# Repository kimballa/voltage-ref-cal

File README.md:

Voltage reference calibration tool
==================================

Precision referenced voltages in 1.000V increments for calibration
of exponential converters in VCOs, VCFs, etc. 

Also usable as a manual GATE/TRIGGER signal generator.

View drawings online:
* [Schematic](https://github.com/kimballa/voltage-ref-cal/blob/main/schematic-rev1.pdf)
* [PCB](https://kicanvas.org/?github=https%3A%2F%2Fgithub.com%2Fkimballa%2Fvoltage-ref-cal%2Fblob%2Fmain%2Fvoltage%2520ref%2520calibration%2520tool.kicad_pcb)

Operation
---------

The rotary switch selects the "baseline voltage" for the output (mono jack J3 and dupont
pins J4), and can set the baseline to between 0 and 5V in 1V increments. 

When pressed, the buttons add further voltages to this; setting the baseline to 4V and
pressing the 2V button will cause the output to jump to 6V. Pressing multiple buttons
at once will sum them up; pressing the 2V and 1V buttons will add 3V to the baseline
as sent to the output, etc. 

The **REF IN** input (J1) takes a voltage input and buffers it; this voltage will be
added to the output when the +IN button is pressed. This reference input voltage can be
any voltage between the power rails, including negative voltages down to -12V.

This device is powered by +/-12VDC input via the Molex MicroFit 3.0 connector J2.  Setting
the power rails at up to +/-18V is acceptable; above this voltage level, the Zener diodes
will exceed power dissipation ratings.  The opamp will also tolerate this level just fine.

Calibration
-----------

Before use, adjust trimpots RV1 and RV2 as follows:

* Set baseline to 5V.
* Give circuit ~60 seconds to warm up.
* Measure output voltage with a DMM.
* Adjust RV1 until output (or test point TP4) reads 5.000V.
* Set baseline to 0V.
* While holding down the +5V button, adjust RV2 until output voltage reads 5.000V.
  (Or measure with DMM at test point TP5 without needing to press the +5V button.) 

Usage tips
----------

### VCO calibration

The primary purpose of the device is to assist in calibration of exponential converters
for VCOs, VCFs, or similar audio equipment. Calibration of this equipment is typically to
establish a 1V / Octave frequency response. Use the knob to set the baseline voltage
at the root of a given octave, and press the +1V button to change the output to the next
octave up in a step-function fashion. This output voltage should be fed as the CV to
the VCO.

An oscilloscope connected to the output of the VCO will show the output waveform. If the
1V/Oct response is maintained, pressing the +1V button will double the frequency and (half
of) the zeroes of the double-frequency waveform will be in the exact same position as the
zeroes of the root-frequency waveform.

Increasing the baseline voltage with the knob allows you to test this 1V / 1 octave step
response throughout the range of the DUT. To test beyond the 6th octave, set the baseline
voltage to 4V and hold down the +2V button to set the baseline at 6V, then press the +1V
button to test the 7V response, etc.

### As standalone GATE / Trigger

To test other functionality of a device that requires a GATE or trigger input, set
the baseline to 0V and press the +5V button to send a GATE signal to the DUT. The +3V
button can be used to trigger devices with a 3.3V logic input. 

Misc
----

Output can be taken from the mono jack or from the pins on connector J4. Both pins of
J4 are the same, and allow easy connection via jumper to breadboard, etc., or connection
of hook-style oscilloscope or DMM probes directly to this board. Matching ground
connection pins are available on J5. 

The output sum will top out at approximately +11.75V (possibly as low as +11V if the
output is used to drive a 2kΩ load). 

If no input is provided to the REF IN jack, it is normaled to ground (+IN button will add
0V to the output).

The rotary switch is a 1-pole, 6-position switch, Alpha MPN `SR1712F-0106-20F0A-N9-N-027`.
This device is now marked obsolete by its mfr; I built with this device because I have
several still on hand. Any 1-deck, 1-pole, 6-position BBM switch with 30 degree position
intervals will do, and there is ample space on the board to fit a different switch
footprint with minimal rerouting of traces. Alpha produces other SR1712F rotary switches
like the 8-position `SR1712F-0108` which can also be dropped in directly. (As-is, the 7th
& 8th positions will cause the baseline voltage to float and the output will be undefined
when the switch is in either of these positions; you could cause the output to be defined
by simply connecting those two pins of the switch to ground.)

License
-------
The voltage reference calibration tool © 2024 by Aaron Kimball is licensed under CC BY-SA
4.0. To view a copy of this license, visit https://creativecommons.org/licenses/by-sa/4.0/

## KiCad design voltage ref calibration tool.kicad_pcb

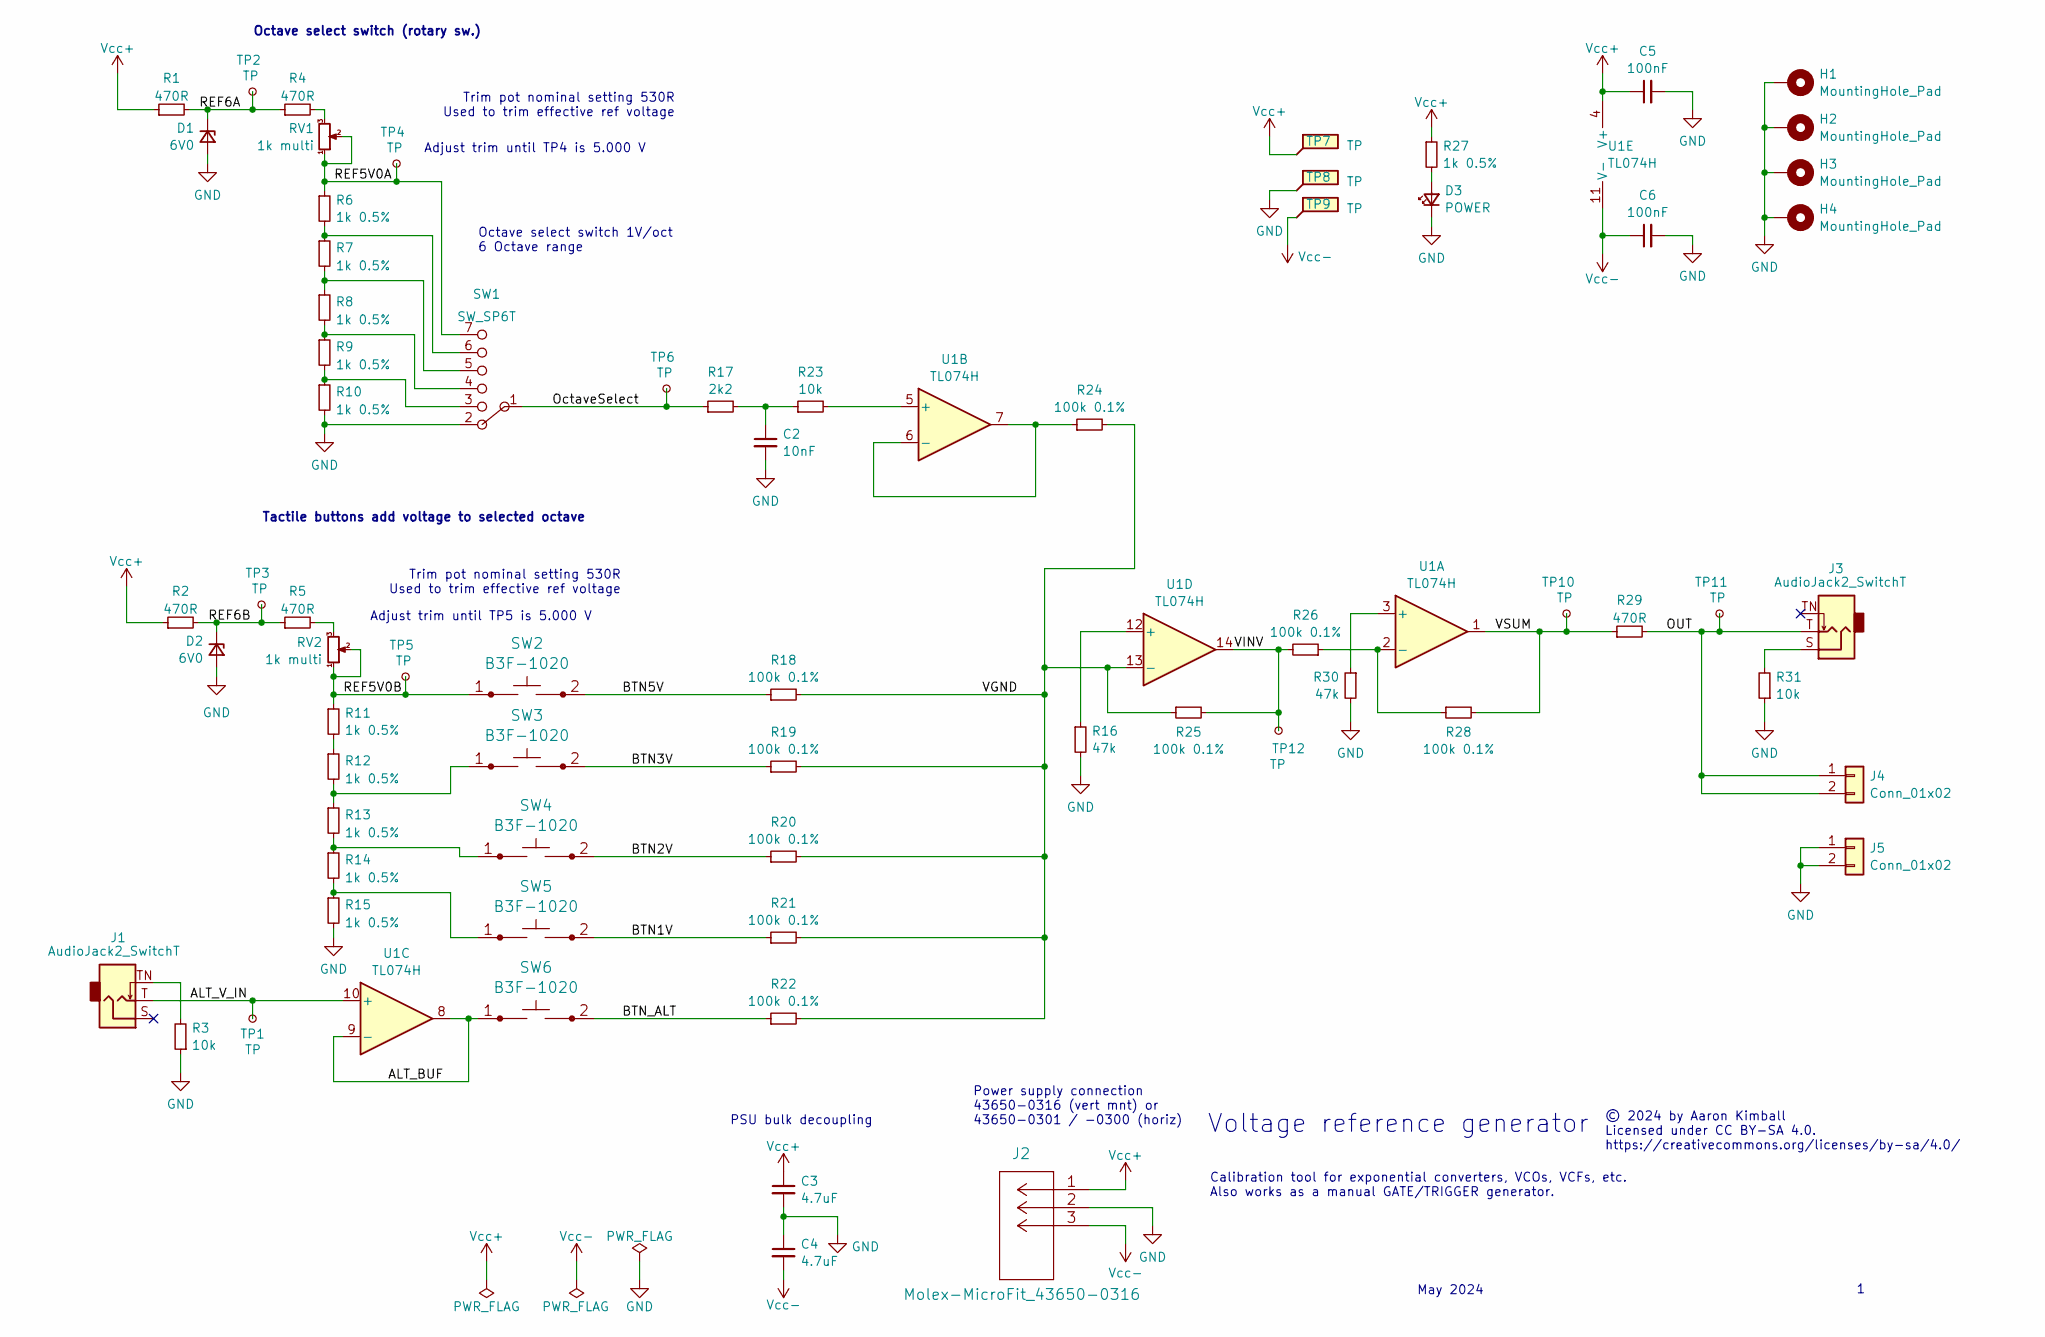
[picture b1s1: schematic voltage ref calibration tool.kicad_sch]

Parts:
C2: 10nF; C_0805_2012Metric_Pad1.18x1.45mm_HandSolder; MPN GRM2165C2A103JA01D
C3, C4: 4.7uF; C_1206_3216Metric_Pad1.33x1.80mm_HandSolder; MPN CL31B475KBHNFNE
C5, C6: 100nF; C_0805_2012Metric_Pad1.18x1.45mm_HandSolder; MPN CL21B104KBFNNNE
D1, D2: 6V0; D_SOD-123_SilkFix; MPN MMSZ5233C-E3-18
D3: POWER; LED_D3.0mm; MPN WP3A8ID
H1, H2, H3, H4: MountingHole_Pad; MountingHole_3.3mm_M3_Full_Standoff_Size
J1, J3: AudioJack2_SwitchT; Schurter-4832.2211; MPN 4832.2211
J2: Molex-MicroFit_43650-0316; Molex-Microfit-43650-0316; MPN 436500316
J4, J5: Conn_01x02; PinHeader_1x02_P2.54mm_Vertical; MPN 5-146850-1
R1, R2, R4, R5, R29: 470R; R_1206_3216Metric_Pad1.30x1.75mm_HandSolder; MPN RC1206FR-7W470RL
R3, R23, R31: 10k; R_0805_2012Metric_Pad1.20x1.40mm_HandSolder; MPN RMCF0805FT10K0
R6, R7, R8, R9, R10, R11, R12, R13, R14, R15, R27: 1k 0.5%; R_1206_3216Metric_Pad1.30x1.75mm_HandSolder; MPN RT1206DRE071KL
R16, R30: 47k; R_0805_2012Metric_Pad1.20x1.40mm_HandSolder; MPN RC0805FR-0747KL
R17: 2k2; R_0805_2012Metric_Pad1.20x1.40mm_HandSolder; MPN CRG0805F2K2
R18, R19, R20, R21, R22, R24, R25, R26, R28: 100k 0.1%; R_0805_2012Metric_Pad1.20x1.40mm_HandSolder; MPN ERA-6AEB104V
RV1, RV2: 1k multi; Pot_Bourns_3214W_SMD_Vert; MPN 3214W-1-102E
SW1: SW_SP6T; Alpha_SR1712F; MPN SR1712F-0106-20F0A-N9-N-027
SW2, SW3, SW4, SW5, SW6: B3F-1020; MPN B3F-1020
TP1, TP2, TP3, TP4, TP5, TP6, TP7, TP8, TP9, TP10, TP11, TP12: TP; TP_HeaderPin_P2.54mm_round
U1: TL074H; TI_SOIC_D_R-PDSO-G14_Wider_Silk; MPN TL074HIDR

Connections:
/ALT_BUF: SW6.1, U1.8, U1.9 (-)
/ALT_V_IN: J1.T, TP1.1, U1.10 (+)
/BTN1V: R21.1, SW5.2
/BTN2V: R20.1, SW4.2
/BTN3V: R19.1, SW3.2
/BTN5V: R18.1, SW2.2
/BTN_ALT: R22.1, SW6.2
/OUT: J3.T, J4.1, J4.2, R29.2, TP11.1
/OctaveSelect: R17.1, SW1.1, TP6.1
/REF5V0A: R6.1, RV1.1, RV1.2, SW1.7, TP4.1
/REF5V0B: R11.1, RV2.1, RV2.2, SW2.1, TP5.1
/REF6A: D1.1 (K), R1.2, R4.1, TP2.1
/REF6B: D2.1 (K), R2.2, R5.1, TP3.1
/VGND: R18.2, R19.2, R20.2, R21.2, R22.2, R24.2, R25.1, U1.13 (-)
/VINV: R25.2, R26.2, TP12.1, U1.14
/VSUM: R28.2, R29.1, TP10.1, U1.1
GND: C2.2, C3.2, C4.1, C5.2, C6.2, D1.2 (A), D2.2 (A), D3.1 (K), H1.1, H2.1, H3.1, H4.1, J2.2, J5.1, J5.2, R3.1, R10.2, R15.2, R16.2, R30.2, R31.1, SW1.2, TP8.1
unnamed: C2.1, R17.2, R23.1
unnamed: D3.2 (A), R27.2
unnamed: J1.TN, R3.2
unnamed: J3.S, R31.2
unnamed: R4.2, RV1.3
unnamed: R5.2, RV2.3
unnamed: R6.2, R7.1, SW1.6
unnamed: R7.2, R8.1, SW1.5
unnamed: R8.2, R9.1, SW1.4
unnamed: R9.2, R10.1, SW1.3
unnamed: R11.2, R12.1
unnamed: R12.2, R13.1, SW3.1
unnamed: R13.2, R14.1, SW4.1
unnamed: R14.2, R15.1, SW5.1
unnamed: R30.1, U1.3 (+)
unnamed: R26.1, R28.1, U1.2 (-)
unnamed: R23.2, U1.5 (+)
unnamed: R24.1, U1.6 (-), U1.7
unnamed: R16.1, U1.12 (+)
Vcc+: C3.1, C5.1, J2.1, R1.1, R2.1, R27.1, TP7.1, U1.4 (V+)
Vcc-: C4.2, C6.1, J2.3, TP9.1, U1.11 (V-)

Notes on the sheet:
May 2024
Trim pot nominal setting 530R Used to trim effective ref voltage
Adjust trim until TP4 is 5.000 V
Octave select switch (rotary sw.)
Power supply connection 43650-0316 (vert mnt) or 43650-0301 / -0300 (horiz)
PSU bulk decoupling
Octave select switch 1V/oct 6 Octave range
© 2024 by Aaron Kimball Licensed under CC BY-SA 4.0. https://creativecommons.org/licenses/by-sa/4.0/
Adjust trim until TP5 is 5.000 V
Calibration tool for exponential converters, VCOs, VCFs, etc. Also works as a manual GATE/TRIGGER generator.
Voltage reference generator
Tactile buttons add voltage to selected octave

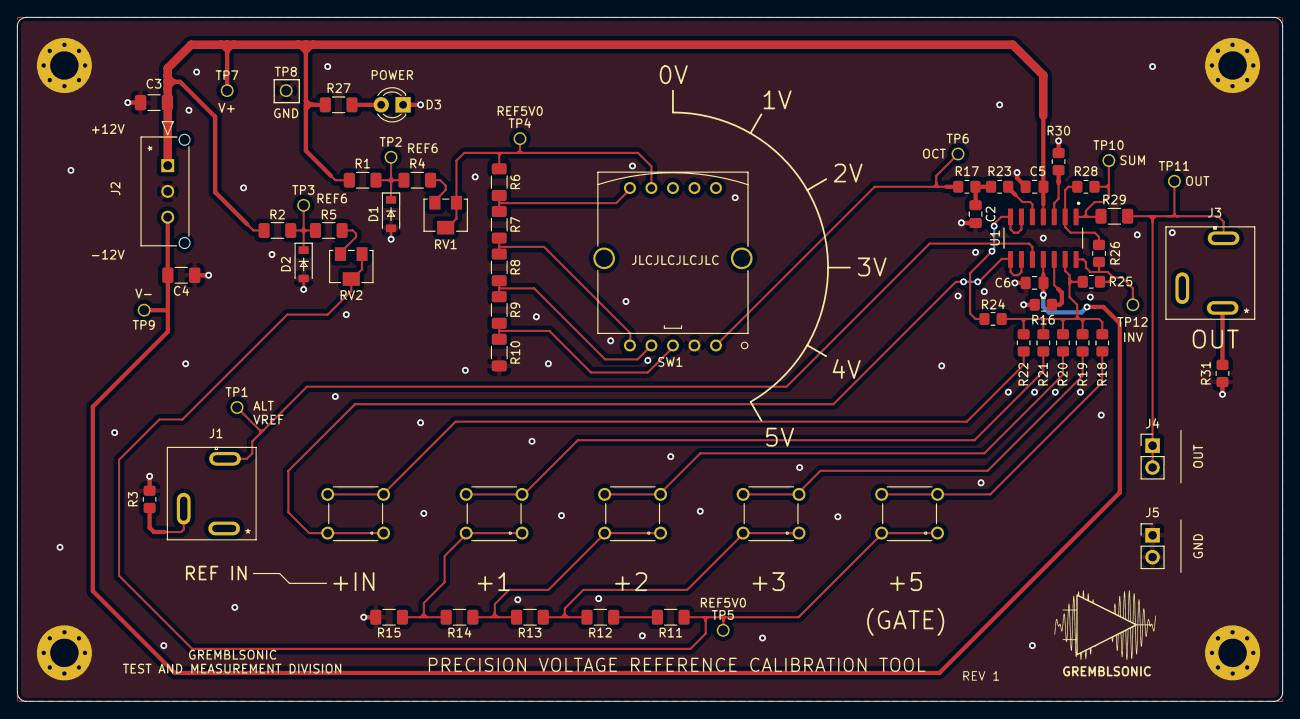
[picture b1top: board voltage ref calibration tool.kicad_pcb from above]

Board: 2 copper layers, 147.1 x 79.5 mm, 69 parts (0 on the bottom side), 38 nets.

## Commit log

2024-05-12 git ignore.
2024-05-12 Add README
2024-05-12 Add empty kicad project.
2024-05-12 Draw schematic.
2024-05-12 Reset annotations.
2024-05-12 route board.
2024-05-12 improve net names.
2024-05-12 don't invert alt ref in
2024-05-13 Some final cleanup. Ready to go.
2024-05-22 Final adjust before gerber generation.
2024-05-22 Add RTM gerbers for rev 1.
2024-05-23 Better readme.
2024-05-23 Add rev1 RTM schematic.
2024-05-23 Add CC BY-SA 4.0 License.
2024-05-23 Add copyright legend to schematic and pcb.
2024-05-23 Add drawing links to readme.
